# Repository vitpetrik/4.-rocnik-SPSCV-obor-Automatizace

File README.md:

# 4. ročník SPŠCV obor Automatizace

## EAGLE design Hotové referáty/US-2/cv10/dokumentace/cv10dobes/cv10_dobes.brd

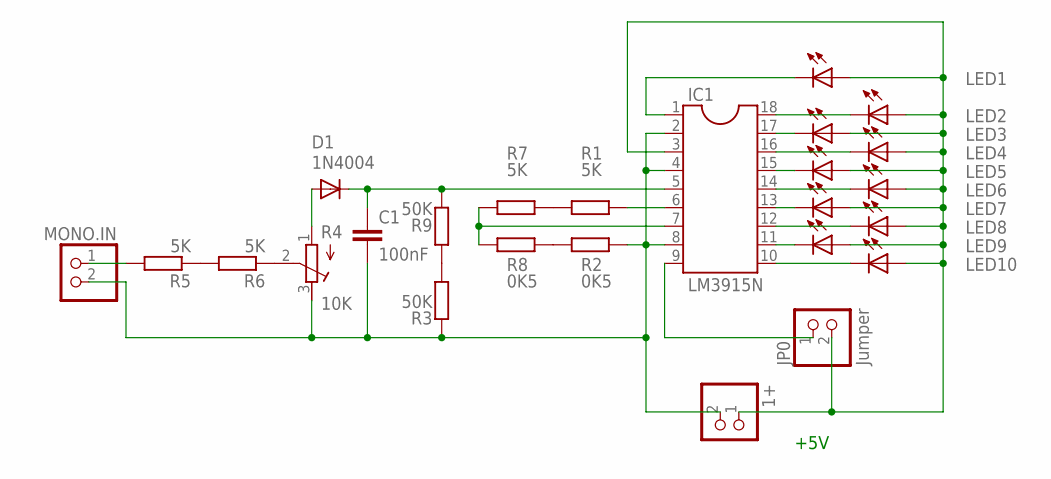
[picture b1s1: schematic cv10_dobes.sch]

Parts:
1+: PINHD-1X2; 1X02
C1: 100nF; C050-030X075
D1: 1N4004; DO41-10
IC1: LM3915N; SOCKET-18
JP0: Jumper; 1X02
LED1, LED2, LED3, LED4, LED5, LED6, LED7, LED8, LED9, LED10: LED5MM
MONO.IN: PINHD-1X2; 1X02
R1, R5, R6, R7: 5K; 0207/7
R2, R8: 0K5; 0207/7
R3, R9: 50K; 0207/7
R4: 10K; RTRIM64P

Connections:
unnamed: MONO.IN.1, R5.2
unnamed: R4.2 (S), R6.1
unnamed: D1.A, R4.1 (E)
unnamed: C1.1, D1.C, IC1.5, R9.2
unnamed: IC1.7, R7.2, R8.2
unnamed: IC1.9, JP0.1
unnamed: IC1.6, R1.1
unnamed: R5.1, R6.2
unnamed: 1+.2, C1.2, IC1.2, IC1.4, IC1.8, MONO.IN.2, R2.1, R3.1, R4.3 (A)
unnamed: 1+.1, IC1.3, JP0.2, LED1.A, LED2.A, LED3.A, LED4.A, LED5.A, LED6.A, LED7.A, LED8.A, LED9.A, LED10.A
unnamed: IC1.1, LED1.K (C)
unnamed: IC1.18, LED2.K (C)
unnamed: IC1.17, LED3.K (C)
unnamed: IC1.16, LED4.K (C)
unnamed: IC1.15, LED5.K (C)
unnamed: IC1.14, LED6.K (C)
unnamed: IC1.13, LED7.K (C)
unnamed: IC1.12, LED8.K (C)
unnamed: IC1.11, LED9.K (C)
unnamed: IC1.10, LED10.K (C)
unnamed: R2.2, R8.1
unnamed: R1.2, R7.1
unnamed: R3.2, R9.1

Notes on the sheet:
+5V

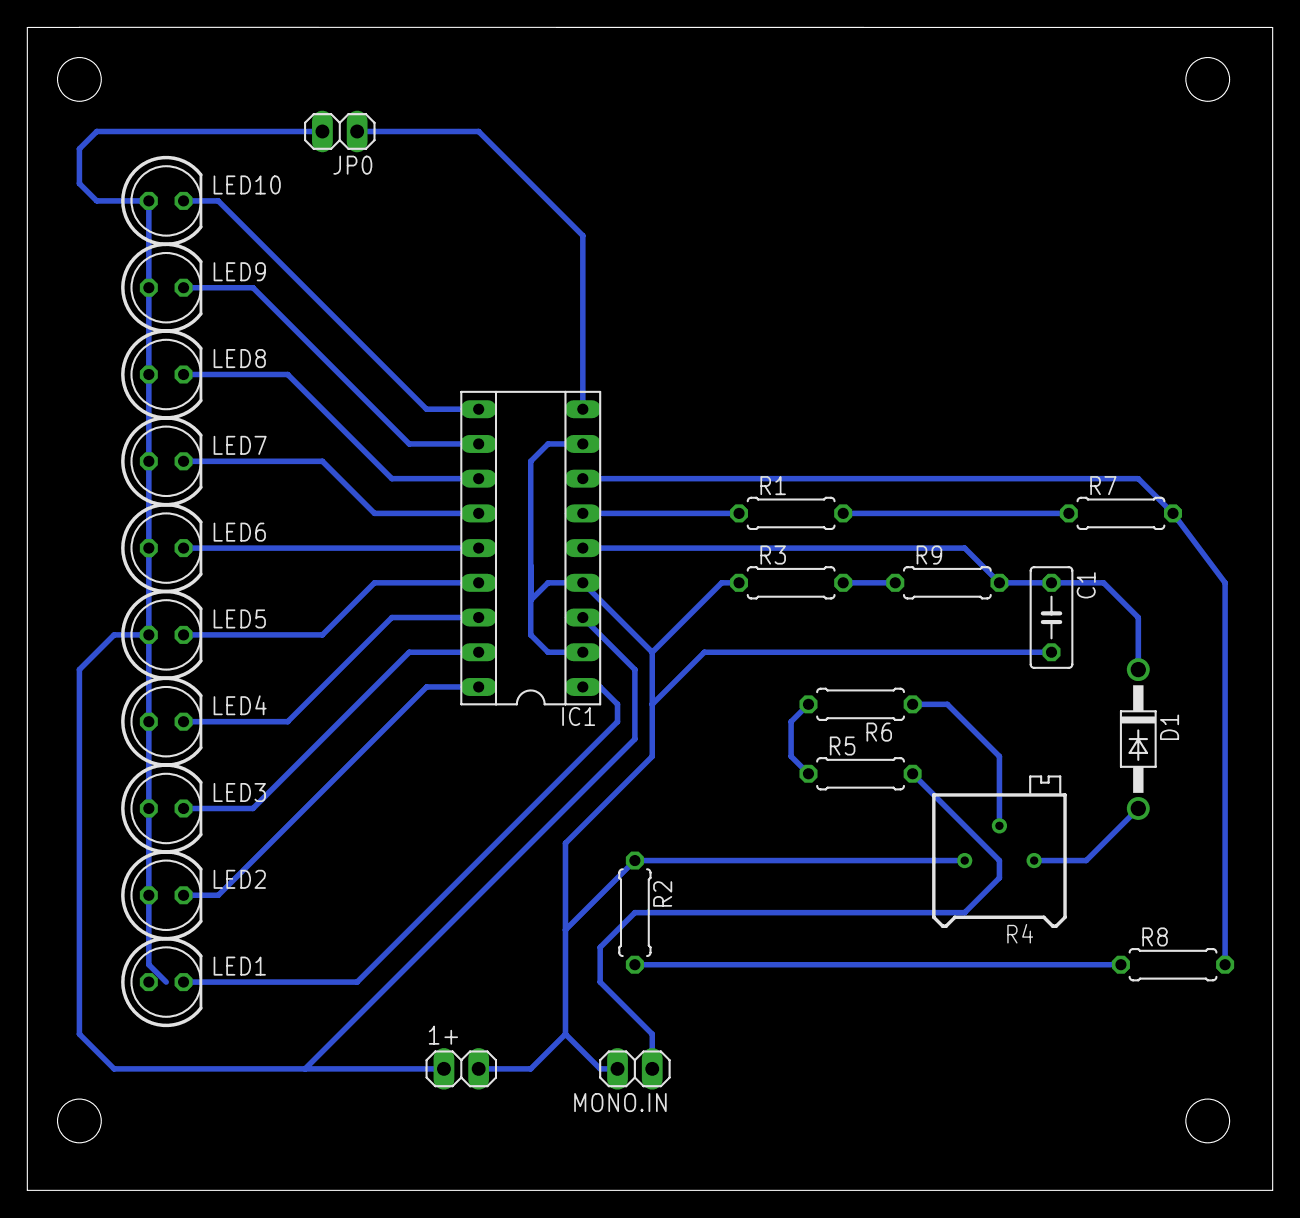
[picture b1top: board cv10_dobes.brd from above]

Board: 2 copper layers, 91.1 x 85.1 mm, 25 parts (0 on the bottom side), 23 nets.

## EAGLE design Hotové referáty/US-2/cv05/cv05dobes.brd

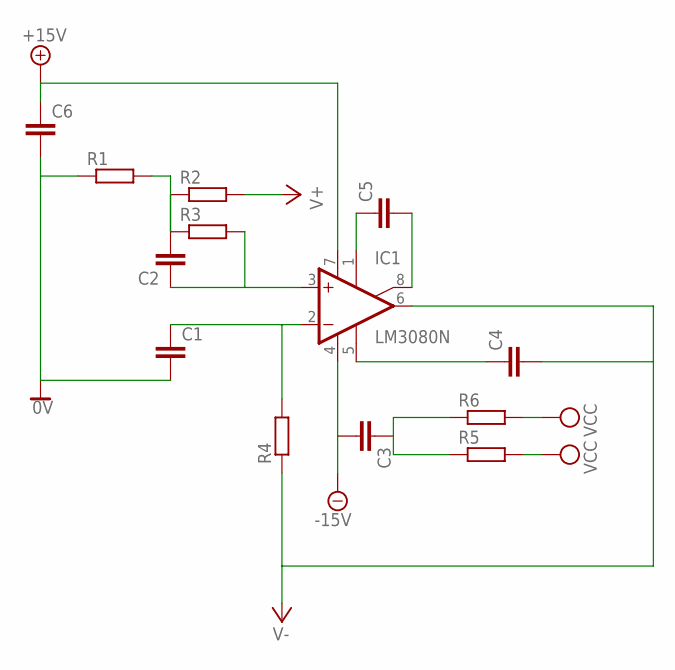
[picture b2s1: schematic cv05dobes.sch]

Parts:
C1, C2: C-EU075-042X103; C075-042X103
C3, C4: C-EU075-052X106; C075-052X106
C5, C6: C-EU050-030X075; C050-030X075
IC1: LM3080N; DIL08
R1, R2, R3, R4: R-EU_0613/15; P0613/15
R5, R6: R-EU_0414/15; 0414/15

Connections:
0V: C1.2, C6.2, R1.1
+15V: C6.1, IC1.7 (V+)
-15V: C3.2, IC1.4 (V-)
unnamed: C5.2, IC1.8 (ON2)
unnamed: C5.1, IC1.1 (ON1)
unnamed: C1.1, IC1.2 (-IN), R4.2
unnamed: C2.1, IC1.3 (+IN), R3.2
unnamed: C2.2, R1.2, R2.1, R3.1
unnamed: R5.1, R6.1
unnamed: C4.1, IC1.5 (OPT)
V+: R2.2
V-: C4.2, IC1.6 (OUT), R4.1
VCC: R5.2, R6.2

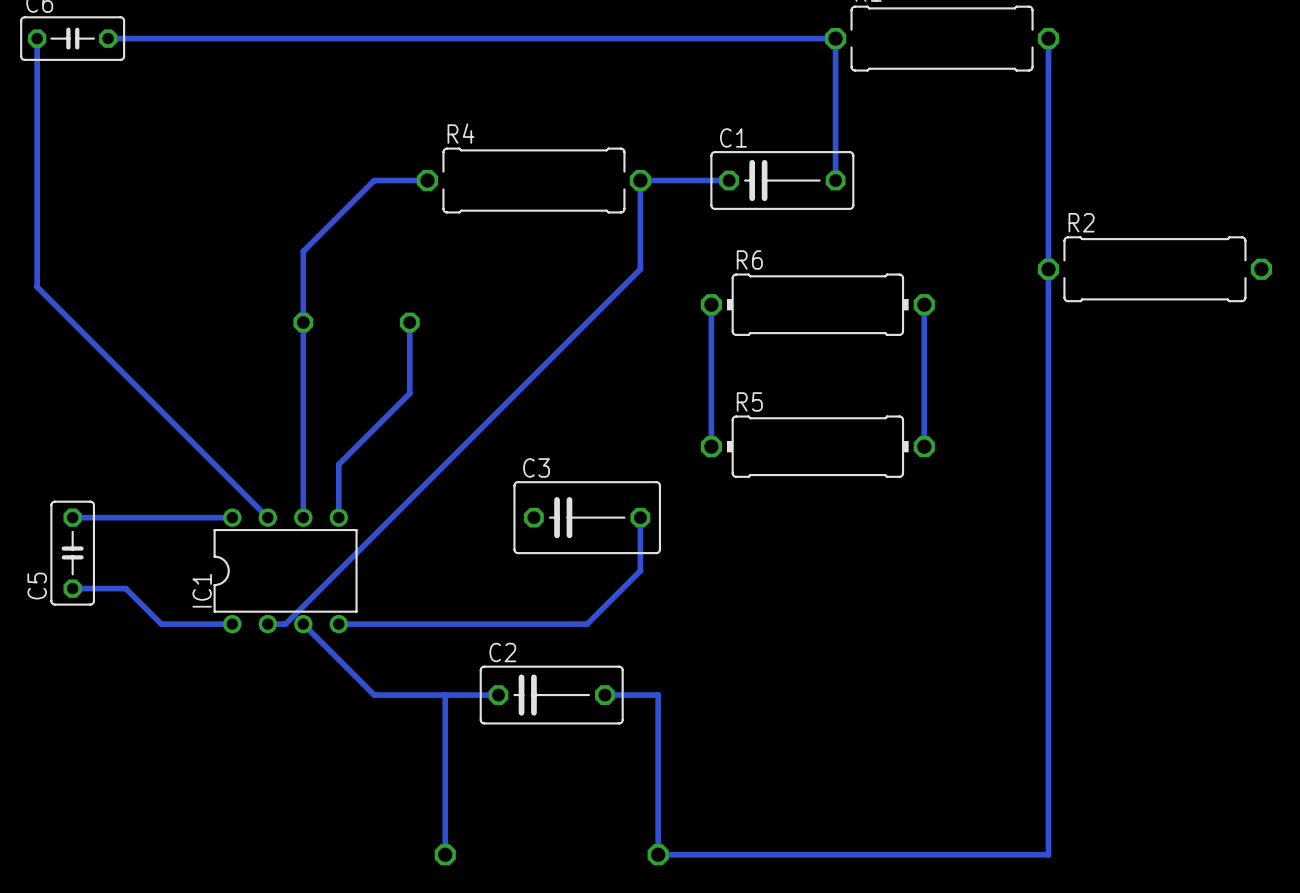
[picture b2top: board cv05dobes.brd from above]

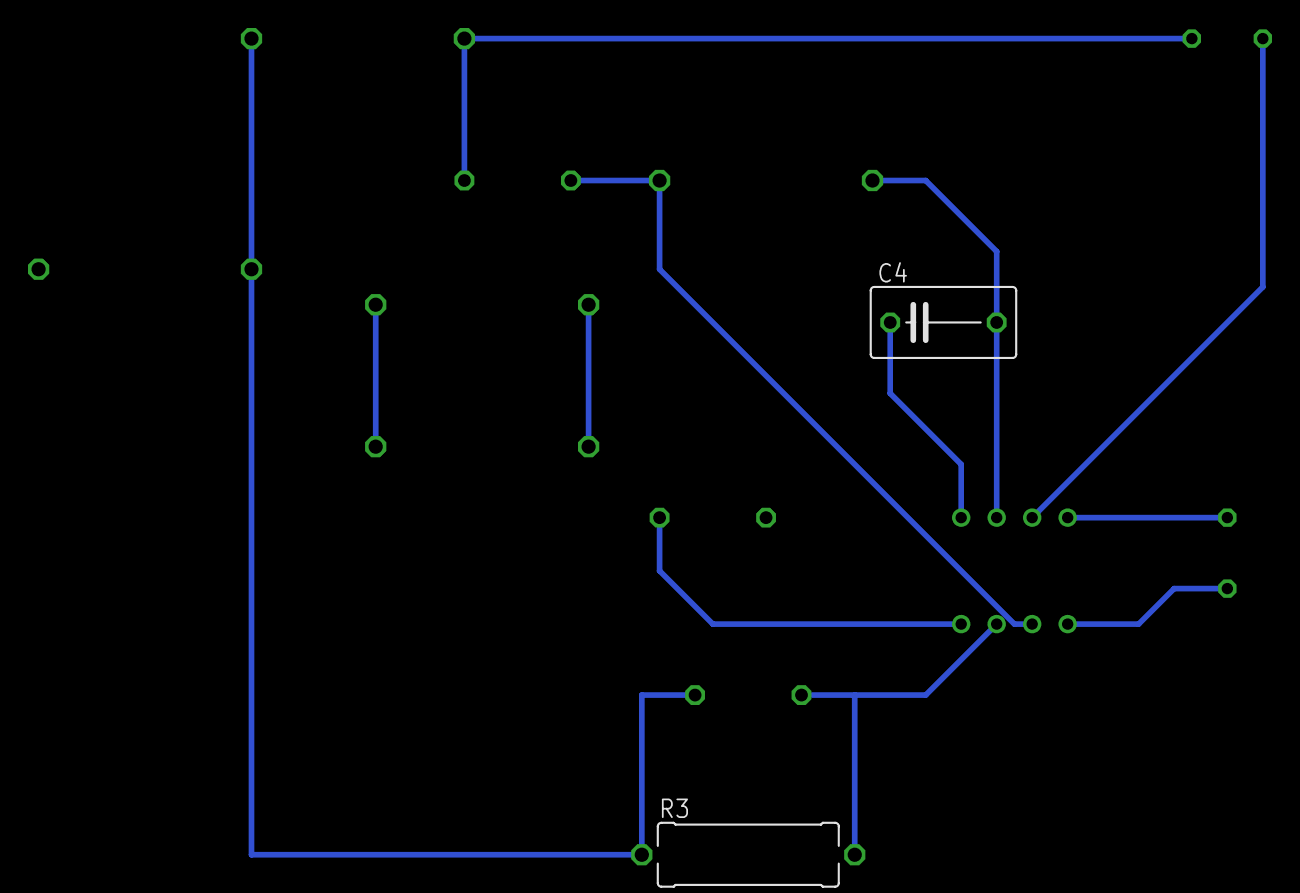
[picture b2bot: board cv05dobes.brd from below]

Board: 2 copper layers, 13 parts (2 on the bottom side), 12 nets.

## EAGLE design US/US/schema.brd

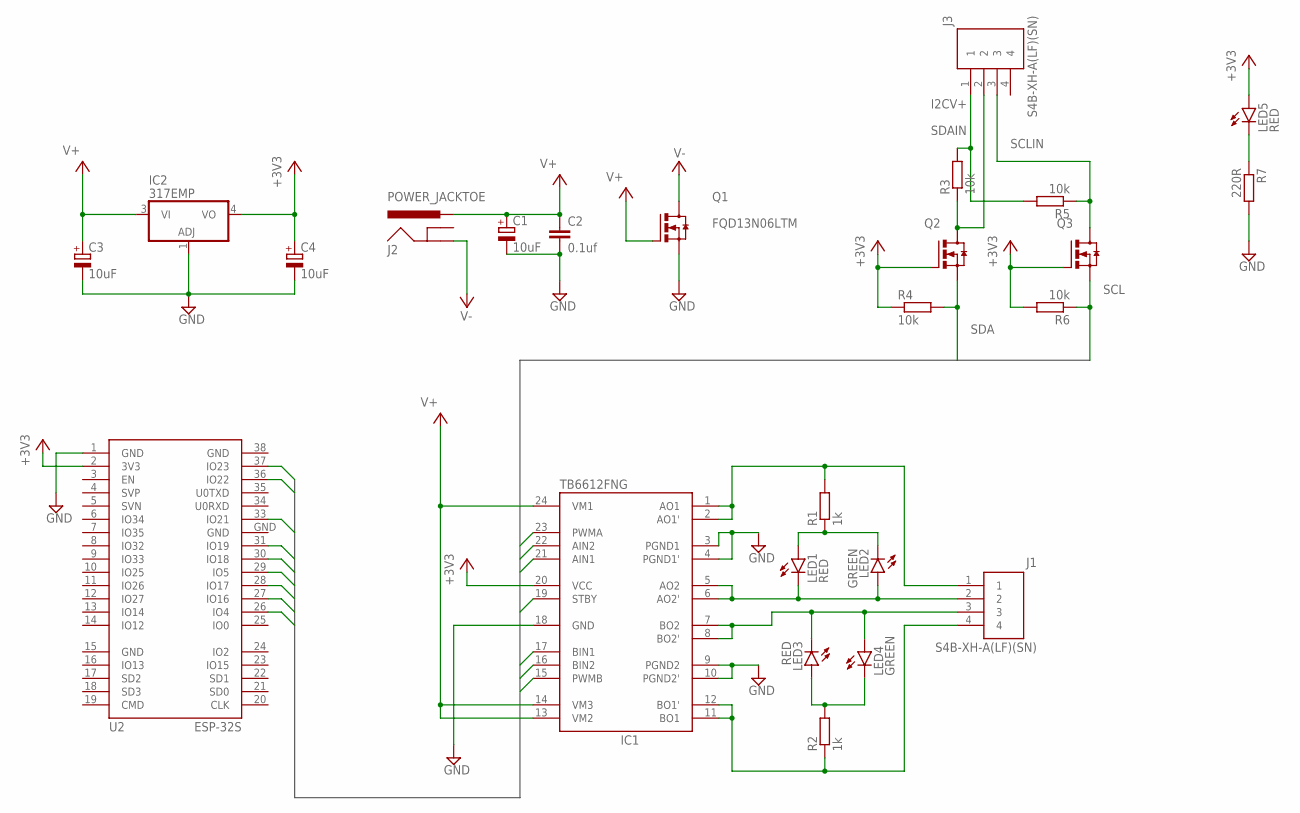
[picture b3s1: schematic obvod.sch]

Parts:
C1: 10uF; 153CLV-0605
C2: 0.1uf; C0805
C3, C4: 10uF; SMC_C
IC1: TB6612FNG; SSOP24
IC2: 317EMP; SOT223
J1, J3: S4B-XH-A(LF)(SN); HDR-04/RA
J2: POWER_JACKTOE; POWER_JACK_SMD_OVERPASTE_TOE
LED1, LED3, LED5: RED; CHIPLED_0805
LED2, LED4: GREEN; CHIPLED_0805
Q1: FQD13N06LTM; DPAK3
Q2, Q3: 2N7002,215; SOT23-3
R1, R2: 1k; R0805
R3, R4, R5, R6: 10k; R0805
R7: 220R; R0805
U2: ESP-32S

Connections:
+3V3: C4.+, IC1.20 (VCC), IC2.4 (VO), LED5.A, Q2.1 (G), Q3.1 (G), R4.1, R6.2, U2.2 (3V3)
AIN1: IC1.21 (AIN1), U2.30 (IO18)
AIN2: IC1.22 (AIN2), U2.29 (IO5)
BIN1: IC1.17 (BIN1), U2.33 (IO21)
BIN2: IC1.16 (BIN2), U2.36 (IO22)
GND: C1.-, C2.2, C3.-, C4.-, IC1.3 (PGND1), IC1.4 (PGND1'), IC1.9 (PGND2), IC1.10 (PGND2'), IC1.18 (GND), IC2.1 (ADJ), Q1.2 (S), R7.2, U2.1 (GND), U2.15 (GND), U2.38 (GND), U2.GND
I2CV+: J3.1, R3.2, R5.2
unnamed: IC1.1 (AO1), IC1.2 (AO1'), J1.1, R1.2
unnamed: IC1.5 (AO2), IC1.6 (AO2'), J1.2, LED1.C, LED2.A
unnamed: IC1.7 (BO2), IC1.8 (BO2'), J1.3, LED3.C, LED4.A
unnamed: IC1.11 (BO1), IC1.12 (BO1'), J1.4, R2.1
unnamed: LED1.A, LED2.C, R1.1
unnamed: LED3.A, LED4.C, R2.2
unnamed: LED5.C, R7.1
PWMA: IC1.23 (PWMA), U2.28 (IO17)
PWMB: IC1.15 (PWMB), U2.37 (IO23)
SCL: Q3.2 (S), R6.1, U2.27 (IO16)
SCLIN: J3.3, Q3.3 (D), R5.1
SDA: Q2.2 (S), R4.2, U2.26 (IO4)
SDAIN: J3.2, Q2.3 (D), R3.1
STBY: IC1.19 (STBY), U2.31 (IO19)
V+: C1.+, C2.1, C3.+, IC1.13 (VM2), IC1.14 (VM3), IC1.24 (VM1), IC2.3 (VI), J2.VIN0 (PWR), Q1.1 (G)
V-: J2.P$4 (GND), Q1.3 (D)

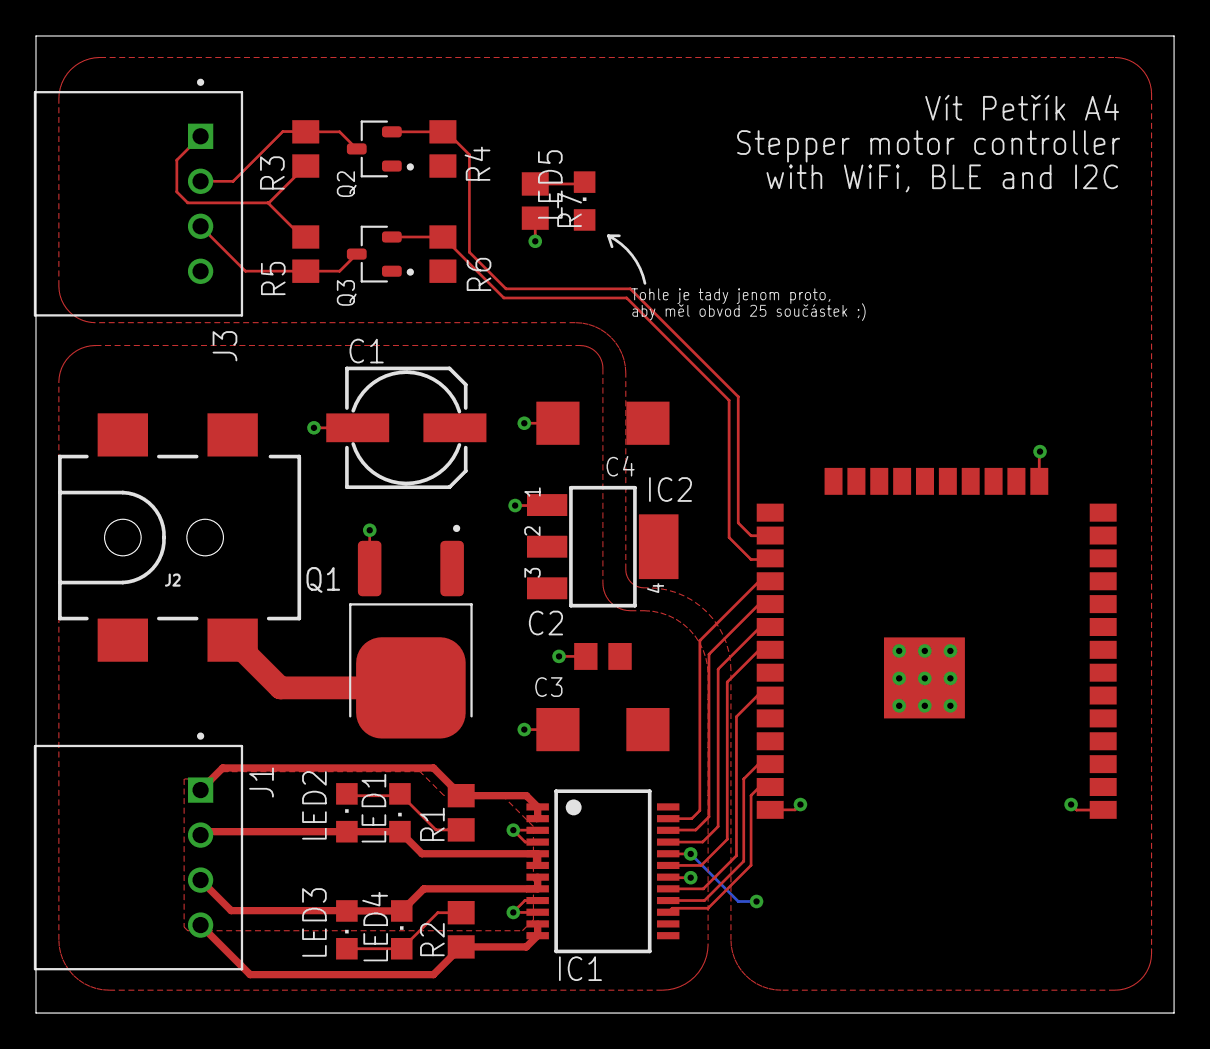
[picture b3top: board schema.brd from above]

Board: 2 copper layers, 63.2 x 54.3 mm, 25 parts (0 on the bottom side), 23 nets.

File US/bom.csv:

Souèást;Hodnota;Device;Package;Description;CREATED_BY;DIGIKEY_PART_NUMBER;MANUFACTURER;MPN;PACKAGE2;POPULARITY;PROD_ID;SF_ID;SPICEPREFIX
C1;10uF;CPOL-EU153CLV-0605;153CLV-0605;POLARIZED CAPACITOR, European symbol;;;;;;5;;;C
C2;0.1uf;C-EUC0805;C0805;CAPACITOR, European symbol;;;;;;88;;;C
C3;10uF;CPOL-EUSMCC;SMC_C;POLARIZED CAPACITOR, European symbol;;;;;;4;;;C
C4;10uF;CPOL-EUSMCC;SMC_C;POLARIZED CAPACITOR, European symbol;;;;;;4;;;C
IC1;-;TB6612FNG;SSOP24;TB6612FNG;;;;;;;;;
IC2;-;317EMP;SOT223;Positive VOLTAGE REGULATOR;;;;;;6;;;
J1;-;S4B-XH-A(LF)(SN);HDR-04/RA;CONN HEADER R/A 4POS 2.5MM;PCBLayout.com;455-2243-ND;JST Sales America Inc.;S4B-XH-A(LF)(SN);;;;;
J2;-;POWER_JACKTOE;POWER_JACK_SMD_OVERPASTE_TOE;Power Jack Connector;;;;;;;CONN-08106;PRT-12748;
J3;-;S4B-XH-A(LF)(SN);HDR-04/RA;CONN HEADER R/A 4POS 2.5MM;PCBLayout.com;455-2243-ND;JST Sales America Inc.;S4B-XH-A(LF)(SN);;;;;
I.01;RED;LEDCHIPLED_0805;CHIPLED_0805;LED;;;;;;52;;;
I.02;GREEN;LEDCHIPLED_0805;CHIPLED_0805;LED;;;;;;52;;;
I.03;RED;LEDCHIPLED_0805;CHIPLED_0805;LED;;;;;;52;;;
I.04;GREEN;LEDCHIPLED_0805;CHIPLED_0805;LED;;;;;;52;;;
I.05;RED;LEDCHIPLED_0805;CHIPLED_0805;LED;;;;;;52;;;
Q1;-;FQD13N06LTM;DPAK3;MOSFET N-CH 60V 11A DPAK;PCBLayout.com;FQD13N06LTMCT-ND;ON Semiconductor;FQD13N06LTM;DPAK-4;;;;
Q2;-;2N7002,215;SOT23-3;MOSFET N-CH 60V 300MA SOT-23;PCBLayout.com;1727-2764-1-ND;Nexperia USA Inc.;2N7002,215;SOT-23-3;;;;
Q3;-;2N7002,215;SOT23-3;MOSFET N-CH 60V 300MA SOT-23;PCBLayout.com;1727-2764-1-ND;Nexperia USA Inc.;2N7002,215;SOT-23-3;;;;
R1;1k;R-EU_R0805;R0805;RESISTOR, European symbol;;;;;;86;;;R
R2;1k;R-EU_R0805;R0805;RESISTOR, European symbol;;;;;;86;;;R
R3;10k;R-EU_R0805;R0805;RESISTOR, European symbol;;;;;;86;;;R
R4;10k;R-EU_R0805;R0805;RESISTOR, European symbol;;;;;;86;;;R
R5;10k;R-EU_R0805;R0805;RESISTOR, European symbol;;;;;;86;;;R
R6;10k;R-EU_R0805;R0805;RESISTOR, European symbol;;;;;;86;;;R
R7;220R;R-EU_R0805;R0805;RESISTOR, European symbol;;;;;;86;;;R
U2;-;ESP-32S;ESP-32S;Ai-Thinker ESP-32S;;;;;;;;;

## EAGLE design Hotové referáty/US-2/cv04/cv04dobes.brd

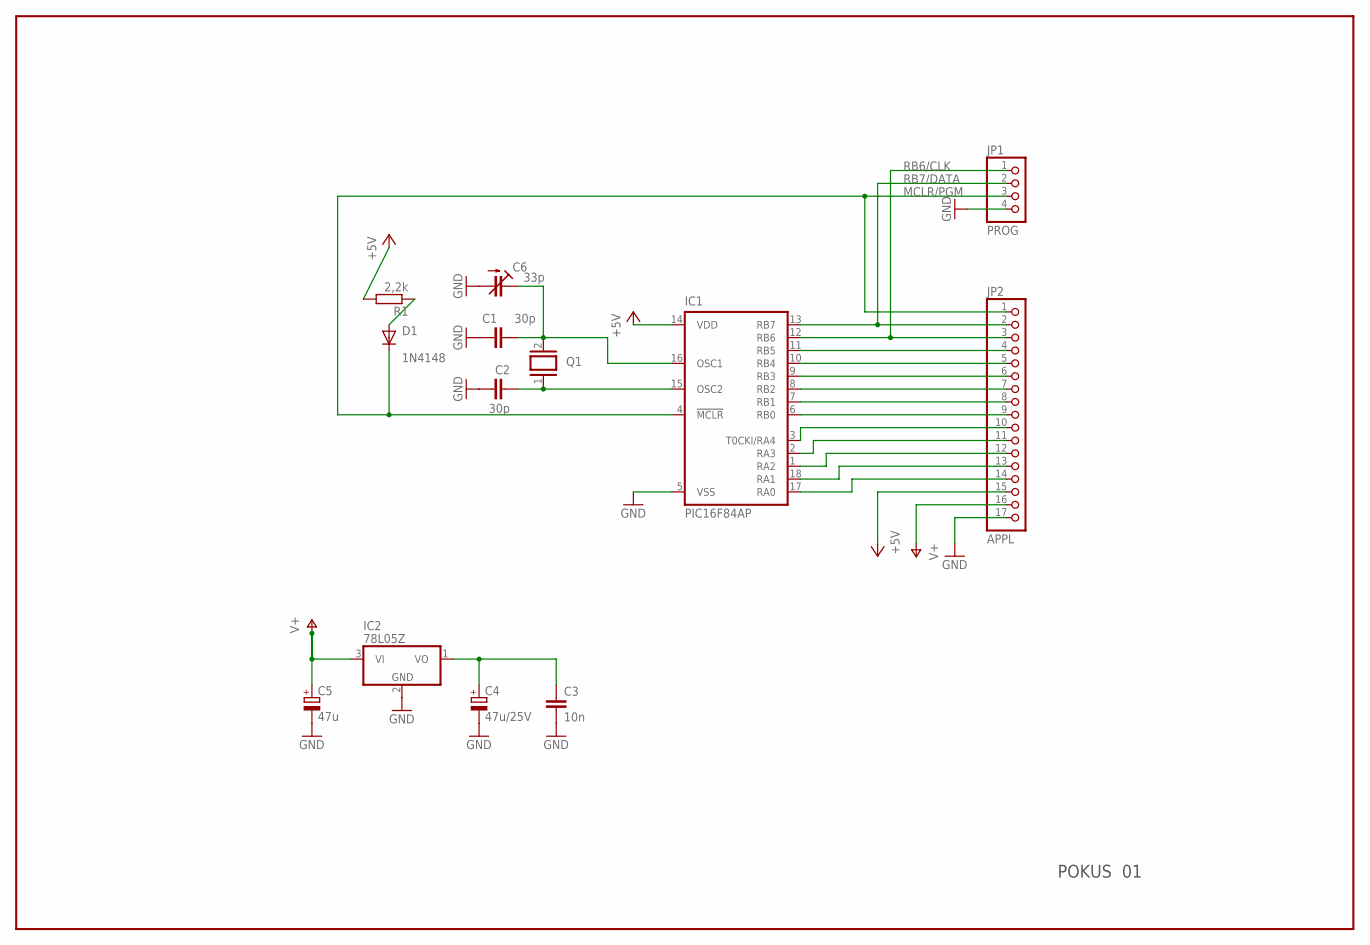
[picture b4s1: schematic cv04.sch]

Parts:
C1, C2: 30p; C025-025X050
C3: 10n; C025-025X050
C4: 47u/25V; TAP5-45
C5: 47u; TAP5-45
C6: 33p; CTRIM3008
D1: 1N4148; DO35-10
IC1: PIC16F84AP; DIL18
IC2: 78L05Z; TO92
JP1: PROG; 1X04
JP2: APPL; 1X17
Q1: XTAL/S; QS
R1: 2,2k; 0207/10

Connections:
+5V: IC1.14 (VDD), JP2.15, R1.2
MCLR/PGM: D1.C, IC1.4 (!MCLR), JP1.3, JP2.1
unnamed: C3.1, C4.+, IC2.1 (VO)
unnamed: C1.2, C6.+ (E), IC1.16 (OSC1), Q1.2
unnamed: C2.2, IC1.15 (OSC2), Q1.1
unnamed: D1.A, R1.1
unnamed: C1.1, C2.1, C3.2, C4.-, C5.-, C6.- (A), IC1.5 (VSS), IC2.2 (GND), JP1.4, JP2.17
RA0: IC1.17 (RA0), JP2.14
RA1: IC1.18 (RA1), JP2.13
RA2: IC1.1 (RA2), JP2.12
RA3: IC1.2 (RA3), JP2.11
RA4: IC1.3 (T0CKI/RA4), JP2.10
RB0: IC1.6 (RB0), JP2.9
RB1: IC1.7 (RB1), JP2.8
RB2: IC1.8 (RB2), JP2.7
RB3: IC1.9 (RB3), JP2.6
RB4: IC1.10 (RB4), JP2.5
RB5: IC1.11 (RB5), JP2.4
RB6/CLK: IC1.12 (RB6), JP1.1, JP2.3
RB7/DATA: IC1.13 (RB7), JP1.2, JP2.2
V+: C5.+, IC2.3 (VI), JP2.16

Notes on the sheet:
POKUS 01

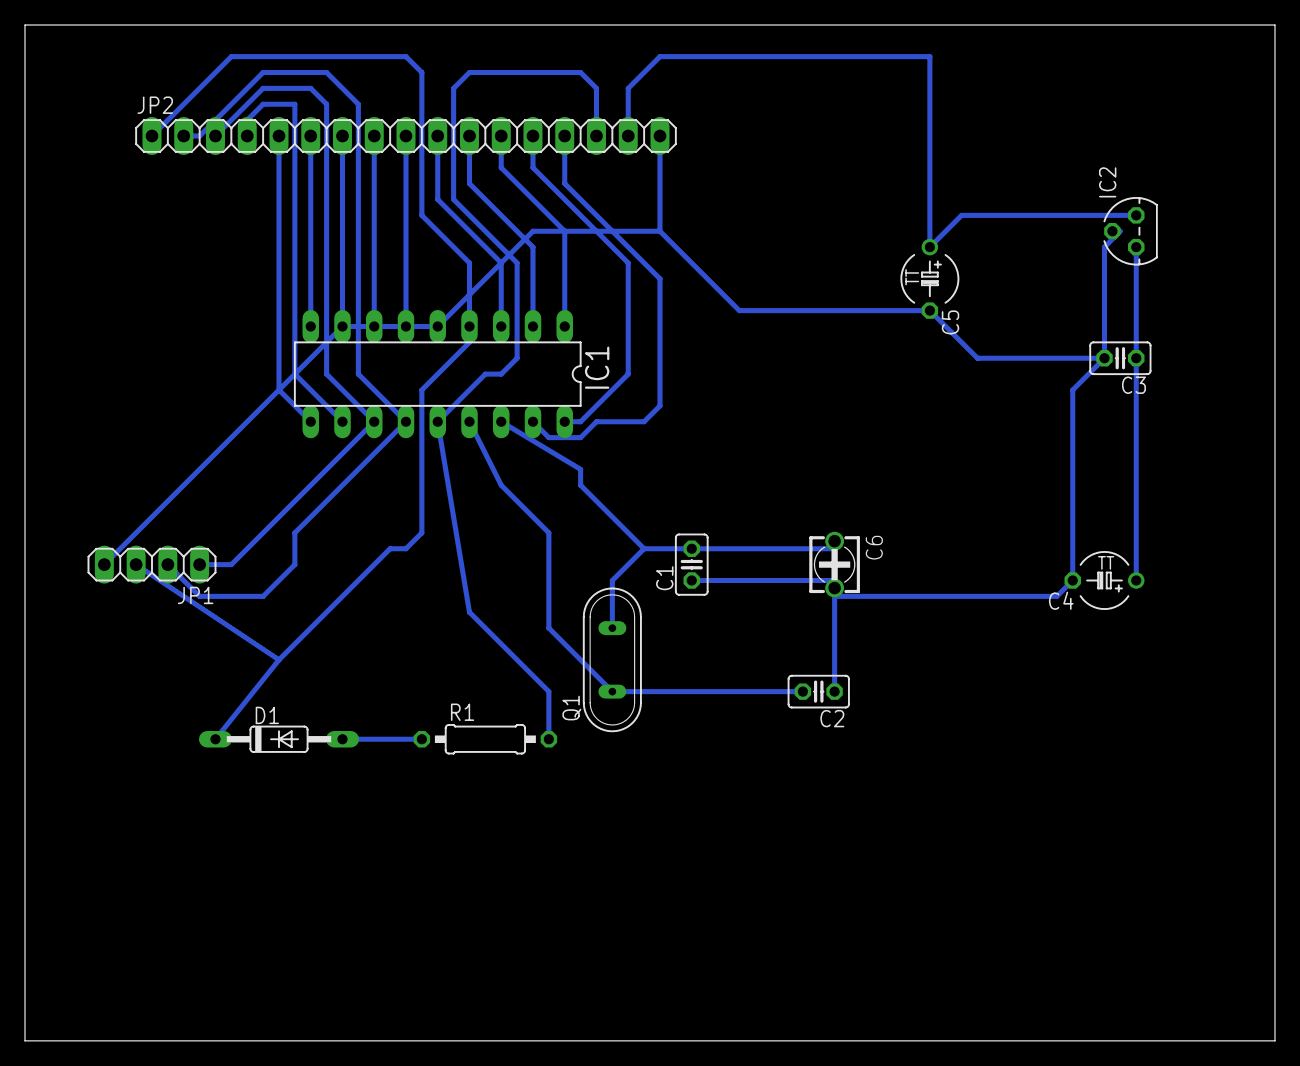
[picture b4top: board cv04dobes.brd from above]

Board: 2 copper layers, 100.0 x 81.3 mm, 13 parts (0 on the bottom side), 21 nets.

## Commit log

2020-02-11 Pridani referatu
2020-02-11 First push
2020-02-11 ELM - Test hradla TTL
2020-02-11 Smazání dektop.ini
2020-02-11 Změna názvů složek
2020-02-11 ACV - uloha 208 Dynast
2020-02-12 Pridani zavorek tak aby program byl funkční 🤣 :+1:
2020-02-16 Referát z výtahu
2020-02-17 Exporty čtenářských deníku do PDF
2020-02-17 Čtenářský deník z Ostře sledovaných vlaků
2020-02-18 Add files via upload
    Zkus mi na to Petříku sáhnout a rozmrdám ti ten tvůj FlyCalc pomocí chyby v zabezpečení při nahrávání obrázků. Nahraji ti tam takovýho porna že ti bude stát celý život.
2020-02-18 Reverát výtah
2020-02-18 Referát ACV - 304
2020-02-19 Začátek alfanumeráku
2020-02-25 ACV 305
2020-02-25 Logický analyzátor
2020-02-25 Zápisy z češtiny
2020-02-25 1.0 alfanum display
2020-02-25 Numericky displej - oprava na 5 znaku
2020-02-25 ELM analyzátor
2020-02-26 Oprava serioveho transferu
2020-02-26 Změny z hodiny
2020-02-26 Uprava konstrukce bufferu
2020-03-02 smrt krasných srncu
2020-03-02 Automatizace ukol
2020-03-03 Uprava ulohy 304 ACV
2020-03-03 Uloha 306 - ACV
2020-03-03 ELM digitalni filtr
2020-03-03 USka
2020-03-03 Pridana konstrukce na zmenu poradi bitu pro opravu pozic na 14 segmentovem displeji
2020-03-03 promotic
2020-03-04 Oprava pozic na 14 segment diepley
2020-03-04 Logicky analyzator na alfanumeraku
2020-03-06 CSVcka z medy
2020-03-08 okomentovany alfanumerak
2020-03-12 Začátek coronaprázdnin
2020-03-12 Zjednoduseni
2020-03-13 Slohova prace
2020-03-13 Úpravy v programu na razeni odporu
2020-03-15 fuzzy logika
2020-03-15 ELM - Otazka č. 16
2020-03-16 Seznam děl na maturitu
2020-03-16 Díla 1. kategorie
2020-03-18 T-norm
2020-03-25 Alfanumerák
2020-03-25 Zadání
2020-03-27 ctenarske deniky
2020-03-27 zivotopis + pruvodni dopis
2020-03-27 ELM otazka 20
2020-03-27 Praxe - samostudium 01
2020-04-01 Krizovatka
2020-04-04 ELM otázka 23
2020-04-14 Úloha s dynastem
2020-04-14 kinematika
2020-04-14 Maturitní otázka č. 24
2020-04-14 Praxe - samostudium 02
2020-04-14 Vyexportovani PDF
2020-04-19 C# program knihovna
2020-04-22 hotovy program knihovny

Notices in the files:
parts and their libraries:
SparkFun-Connectors: Licensing: Creative Commons ShareAlike 4.0 International - https://creativecommons.org/licenses/by-sa/4.0
esp32: Creative Commons Attribution-ShareAlike 4.0 International
